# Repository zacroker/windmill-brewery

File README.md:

# windmill-brewery
This is a work in progress of my home brew tinkering with some electronics to enhance the experience

To get started clone this repo and initialise the submodules

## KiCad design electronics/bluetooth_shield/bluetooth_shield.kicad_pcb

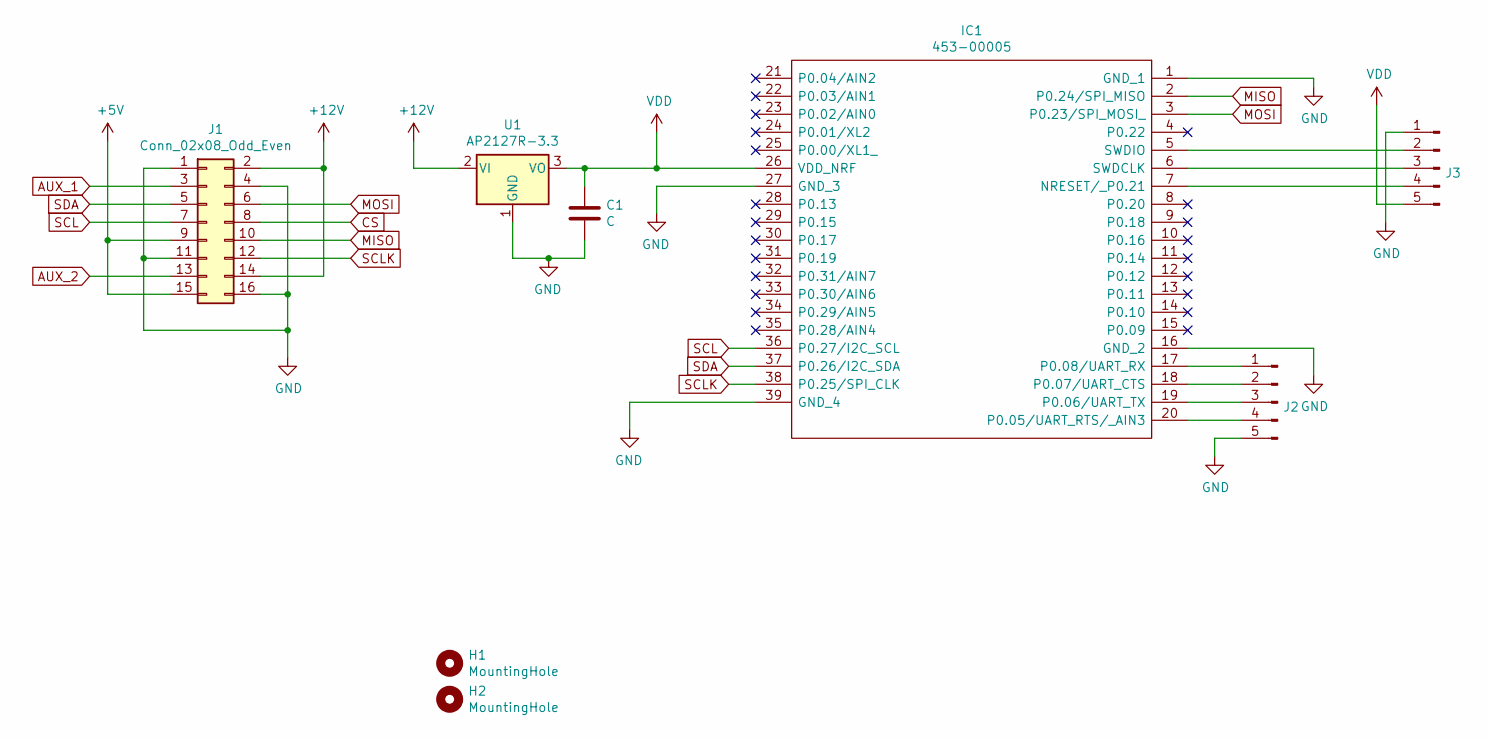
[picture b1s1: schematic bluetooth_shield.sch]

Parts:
C1: C; C_0805_2012Metric_Pad1.18x1.45mm_HandSolder
H1, H2: MountingHole; MountingHole_3.2mm_M3_DIN965_Pad_TopBottom
IC1: 453-00005; 45300005; Manufacturer_Part_Number 453-00005; Mouser Part Number 239-453-00005
J1: Conn_02x08_Odd_Even; PinHeader_2x08_P2.54mm_Vertical
J2, J3: Conn_01x05_Male; PinHeader_1x05_P2.54mm_Vertical
U1: AP2127R-3.3; SOT-89-3

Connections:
+5V: J1.9, J1.15
+12V: J1.2, J1.14, U1.2 (VI)
AUX_1: J1.3
AUX_2: J1.13
CS: J1.8
GND: C1.2, IC1.1 (GND_1), IC1.16 (GND_2), IC1.27 (GND_3), IC1.39 (GND_4), J1.1, J1.4, J1.11, J1.16, J2.5, J3.1, U1.1 (GND)
MISO: IC1.2 (P0.24/SPI_MISO), J1.10
MOSI: IC1.3 (P0.23/SPI_MOSI_), J1.6
unnamed: IC1.5 (SWDIO), J3.2
unnamed: IC1.6 (SWDCLK), J3.3
unnamed: IC1.7 (NRESET/_P0.21), J3.4
unnamed: IC1.17 (P0.08/UART_RX), J2.1
unnamed: IC1.18 (P0.07/UART_CTS), J2.2
unnamed: IC1.19 (P0.06/UART_TX), J2.3
unnamed: IC1.20 (P0.05/UART_RTS/_AIN3), J2.4
SCL: IC1.36 (P0.27/I2C_SCL), J1.7
SCLK: IC1.38 (P0.25/SPI_CLK), J1.12
SDA: IC1.37 (P0.26/I2C_SDA), J1.5
VDD: C1.1, IC1.26 (VDD_NRF), J3.5, U1.3 (VO)

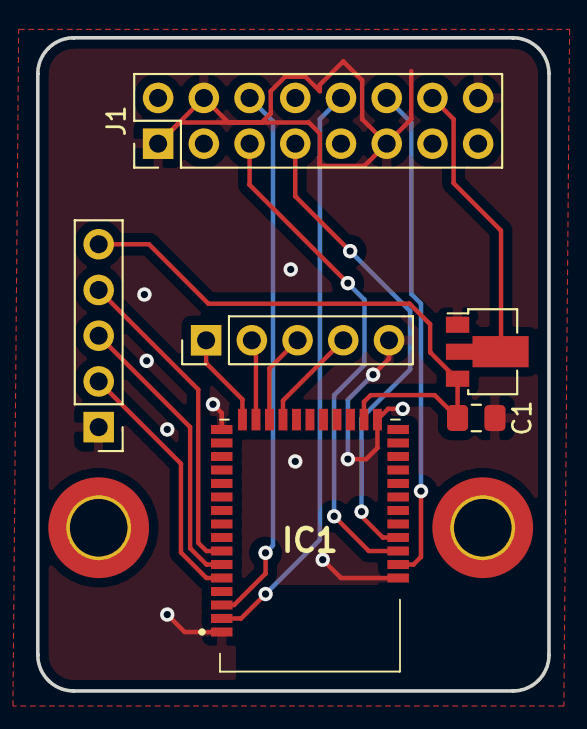
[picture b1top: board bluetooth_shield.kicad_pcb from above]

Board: 2 copper layers, 28.4 x 36.3 mm, 8 parts (0 on the bottom side), 16 nets.

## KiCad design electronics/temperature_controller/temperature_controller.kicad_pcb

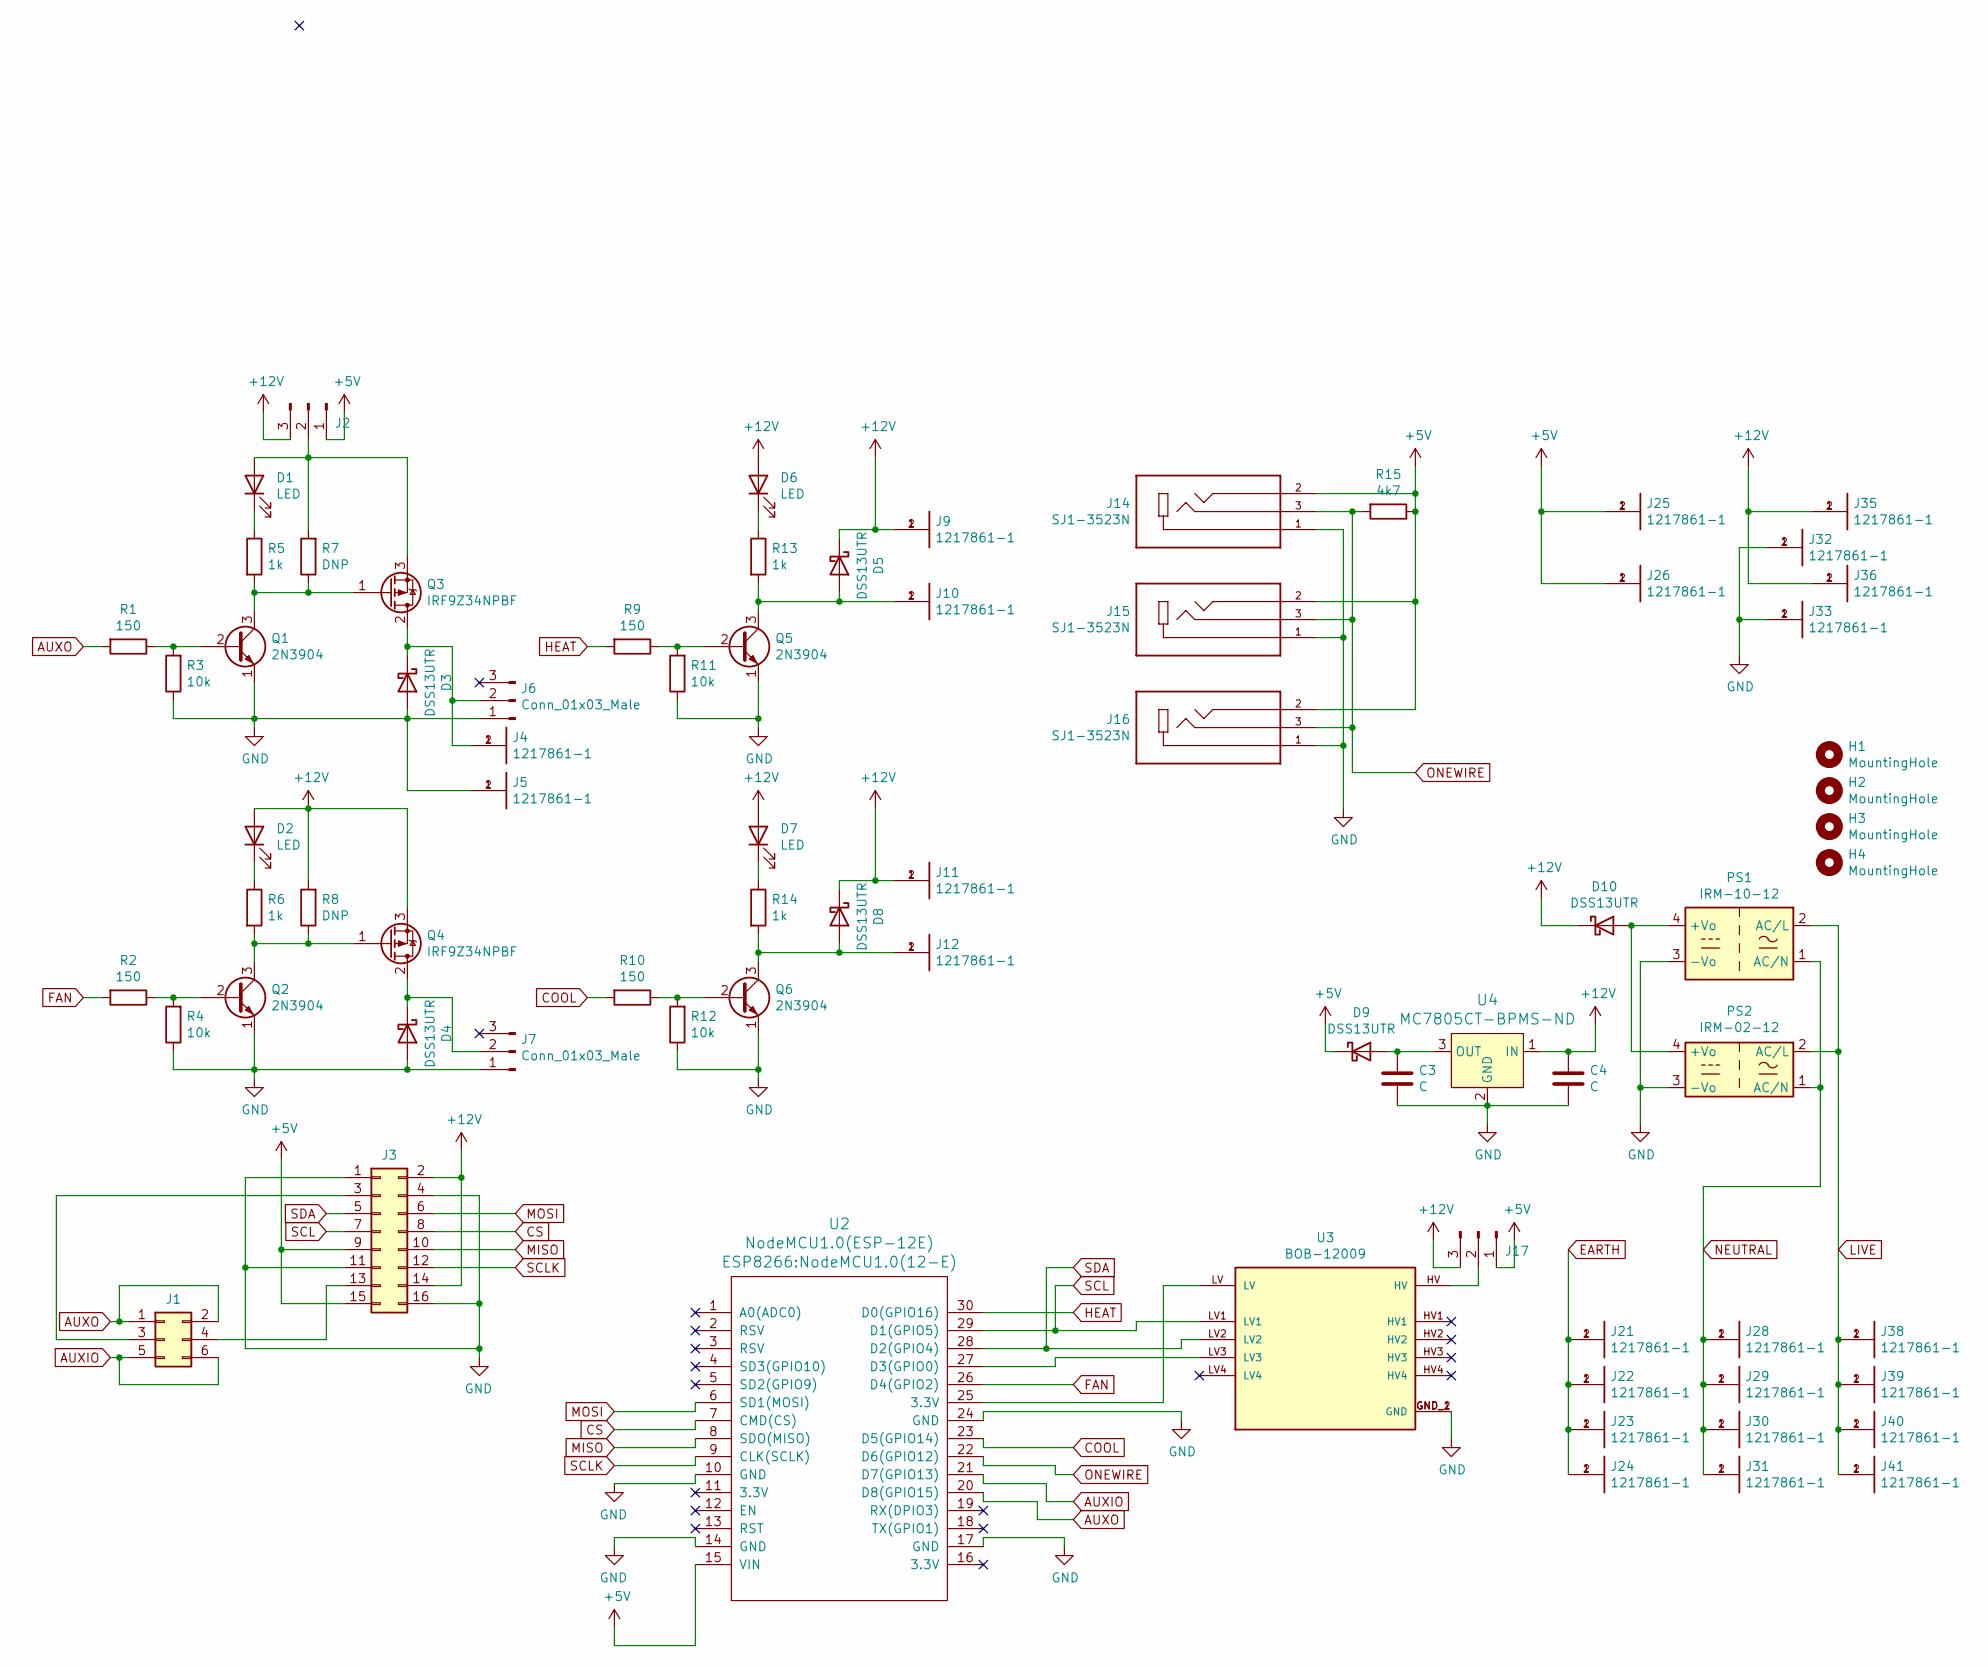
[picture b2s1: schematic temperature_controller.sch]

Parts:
C3, C4: C; C_Disc_D8.0mm_W2.5mm_P5.00mm
D1, D2, D6, D7: LED; LED_D3.0mm
D3, D4, D5, D8, D9, D10: ‎DSS13UTR‎; D_SOD-123F
H1, H2, H3, H4: MountingHole; MountingHole_3.2mm_M3_Pad_TopBottom
J1: Conn_02x03_Odd_Even; PinHeader_2x03_P2.54mm_Vertical
J2, J6, J7, J17: Conn_01x03_Male; PinHeader_1x03_P2.54mm_Vertical
J3: Conn_02x08_Odd_Even; PinHeader_2x08_P2.54mm_Vertical
J4, J5, J9, J10, J11, J12, J21, J22, J23, J24, J25, J26, J28, J29, J30, J31, J32, J33, J35, J36, J38, J39, J40, J41: 1217861-1; TE_1217861-1
J14, J15, J16: SJ1-3523N; CUI_SJ1-3523N; PARTREV 1.02
PS1: IRM-10-12; Converter_ACDC_MeanWell_IRM-10-xx_THT
PS2: IRM-02-12; Converter_ACDC_MeanWell_IRM-02-xx_THT
Q1, Q2, Q5, Q6: 2N3904; TO-92_Inline
Q3, Q4: IRF9Z34NPBF; TO-220-3_Vertical
R1, R2, R9, R10: 150; R_0805_2012Metric_Pad1.20x1.40mm_HandSolder
R3, R4, R11, R12: 10k; R_0805_2012Metric_Pad1.20x1.40mm_HandSolder
R5, R6, R13, R14: 1k; R_0805_2012Metric_Pad1.20x1.40mm_HandSolder
R7, R8: DNP; R_0805_2012Metric_Pad1.20x1.40mm_HandSolder
R15: 4k7; R_0805_2012Metric_Pad1.20x1.40mm_HandSolder
U2: NodeMCU1.0(ESP-12E); NodeMCU1.0(12-E)
U3: BOB-12009; CONV_BOB-12009; PARTREV 01
U4: MC7805CT-BPMS-ND; TO-220-3_Vertical

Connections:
+5V: D9.1 (K), J2.1, J3.9, J3.15, J14.2, J15.2, J16.2, J17.1, J25.1, J25.2, J26.1, J26.2, R15.1, U2.15 (VIN); also elsewhere on the board
+12V: C4.1, D2.2 (A), D5.1 (K), D6.2 (A), D7.2 (A), D8.1 (K), D10.1 (K), J2.3, J3.2, J3.14, J9.1, J9.2, J11.1, J11.2, J17.3, J35.1, J35.2, J36.1, J36.2, Q4.3 (S), R8.2, U4.1 (IN); also elsewhere on the board
AUXIO: J1.5, J1.6, U2.21 (D7(GPIO13))
AUXO: J1.1, J1.2, R1.2, U2.20 (D8(GPIO15))
COOL: R10.2, U2.23 (D5(GPIO14))
CS: J3.8, U2.7 (CMD(CS))
EARTH: J21.1, J21.2, J22.1, J22.2, J23.1, J23.2, J24.1, J24.2
FAN: R2.2, U2.26 (D4(GPIO2))
GND: C3.2, C4.2, D3.2 (A), D4.2 (A), J3.1, J3.4, J3.11, J3.16, J5.1, J5.2, J6.1, J7.1, J14.1, J15.1, J16.1, J32.1, J32.2, J33.1, J33.2, PS1.3 (-Vo), PS2.3 (-Vo), Q1.1 (E), Q2.1 (E), Q5.1 (E), Q6.1 (E), R3.1, R4.1, R11.1, R12.1, U2.10 (GND), U2.14 (GND), U2.17 (GND), U2.24 (GND), U3.GND_1 (GND), U3.GND_2 (GND), U4.2 (GND); also elsewhere on the board
HEAT: R9.2, U2.30 (D0(GPIO16))
LIVE: J38.1, J38.2, J39.1, J39.2, J40.1, J40.2, J41.1, J41.2, PS1.2 (AC/L), PS2.2 (AC/L)
MISO: J3.10, U2.8 (SDO(MISO))
MOSI: J3.6, U2.6 (SD1(MOSI))
NEUTRAL: J28.1, J28.2, J29.1, J29.2, J30.1, J30.2, J31.1, J31.2, PS1.1 (AC/N), PS2.1 (AC/N)
unnamed: C3.1, D9.2 (A), U4.3 (OUT)
unnamed: D1.1 (K), R5.1
unnamed: D1.2 (A), J2.2, Q3.3 (S), R7.2
unnamed: D2.1 (K), R6.1
unnamed: D3.1 (K), J4.1, J4.2, J6.2, Q3.2 (D)
unnamed: D4.1 (K), J7.2, Q4.2 (D)
unnamed: D5.2 (A), J10.1, J10.2, Q5.3 (C), R13.2
unnamed: D6.1 (K), R13.1
unnamed: D7.1 (K), R14.1
unnamed: D8.2 (A), J12.1, J12.2, Q6.3 (C), R14.2
unnamed: D10.2 (A), PS1.4 (+Vo), PS2.4 (+Vo)
unnamed: J1.3, J3.3
unnamed: J1.4, J3.13
unnamed: J17.2, U3.HV
unnamed: Q1.2 (B), R1.1, R3.2
unnamed: Q1.3 (C), Q3.1 (G), R5.2, R7.1
unnamed: Q2.2 (B), R2.1, R4.2
unnamed: Q2.3 (C), Q4.1 (G), R6.2, R8.1
unnamed: Q5.2 (B), R9.1, R11.2
unnamed: Q6.2 (B), R10.1, R12.2
unnamed: U2.25 (3.3V), U3.LV
unnamed: U2.27 (D3(GPIO0)), U3.LV3
ONEWIRE: J14.3, J15.3, J16.3, R15.2, U2.22 (D6(GPIO12))
SCL: J3.7, U2.29 (D1(GPIO5)), U3.LV1
SCLK: J3.12, U2.9 (CLK(SCLK))
SDA: J3.5, U2.28 (D2(GPIO4)), U3.LV2

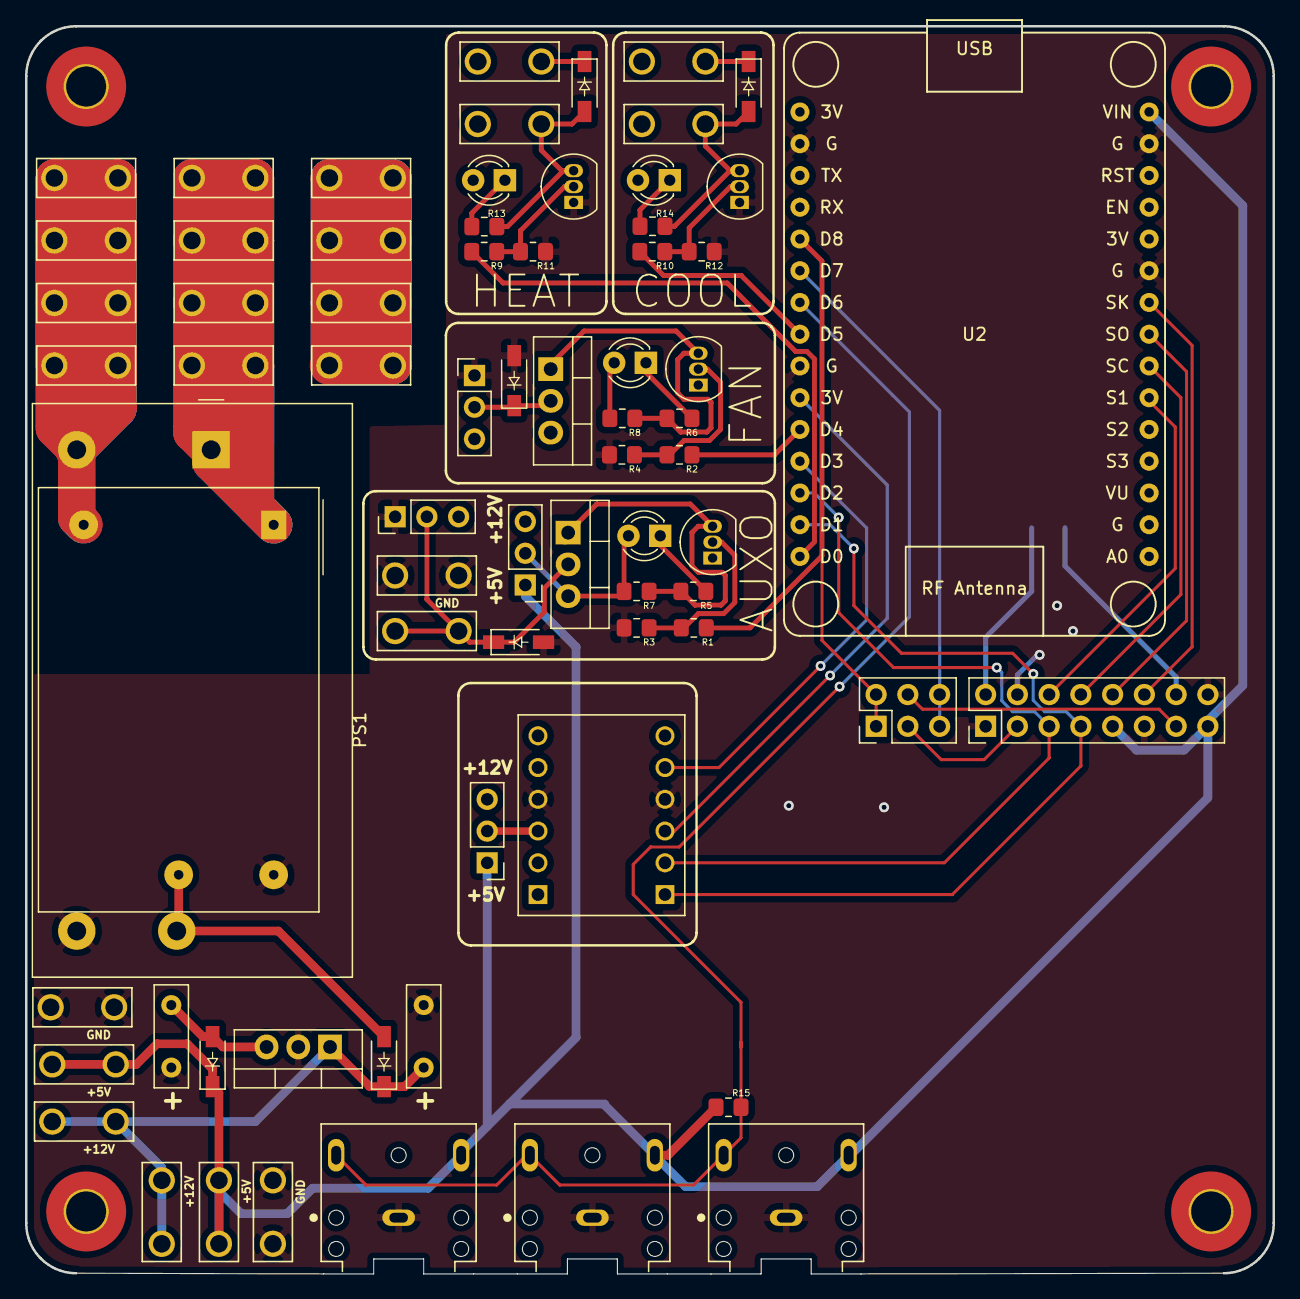
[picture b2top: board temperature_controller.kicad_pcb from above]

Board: 2 copper layers, 99.8 x 99.8 mm, 75 parts (0 on the bottom side), 40 nets.

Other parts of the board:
+5V, +5V#2, +12V, +12V#2: 1217861-1; TE_1217861-1
GND: 1217861-1; TE_1217861-1
GND#2, GND#3: 1217861-1; TE_1217861-1

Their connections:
+5V: +5V.1, +5V.2, +5V#2.1, +5V#2.2; also elsewhere on the board
+12V: +12V.1, +12V.2, +12V#2.1, +12V#2.2; also elsewhere on the board
GND: GND.1, GND.2, GND#2.1, GND#2.2, GND#3.1, GND#3.2; also elsewhere on the board

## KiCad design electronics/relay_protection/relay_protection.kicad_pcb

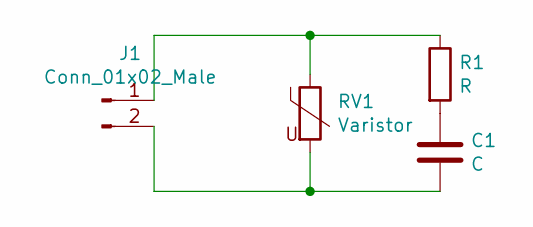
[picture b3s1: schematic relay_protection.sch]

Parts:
C1: C; C_Axial_L12.0mm_D8.5mm_P15.00mm_Horizontal
J1: Conn_01x02_Male; SolderWire-2.5sqmm_1x02_P8.8mm_D2.4mm_OD4.4mm_Relief2x
R1: R; R_Axial_DIN0411_L9.9mm_D3.6mm_P15.24mm_Horizontal
RV1: Varistor; RV_Disc_D12mm_W4.4mm_P7.5mm

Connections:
unnamed: C1.1, R1.2
unnamed: C1.2, J1.2, RV1.2
unnamed: J1.1, R1.1, RV1.1

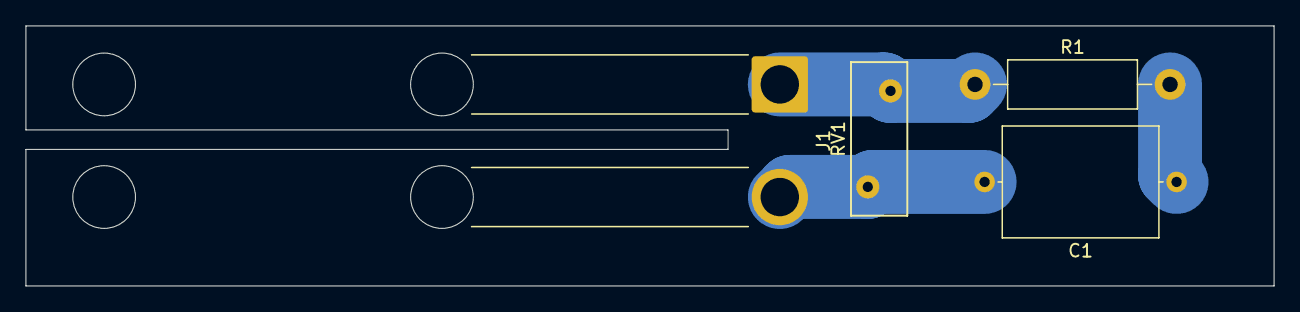
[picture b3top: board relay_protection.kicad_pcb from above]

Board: 2 copper layers, 97.5 x 20.3 mm, 4 parts (0 on the bottom side), 3 nets.

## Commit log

2021-09-24 quick and dirty micropython and bluetooth serial kegerator controller
2021-09-24 prepare for electronics
2021-09-24 first run at temperature controller schematic with pi pico
2021-09-25 add kicad esp submodule
2021-09-25 Adding a very basic readme
2021-09-25 finish board schematics
2021-09-26 update footprints, schematic and start board layout
2021-09-26 finished layout move to bluetooth shield
2021-09-26 Update schematics for bluetooth breakout shield
2021-09-30 Updating layouts and schematics and reading for export
2021-10-04 Updating layouts for better shield addition
